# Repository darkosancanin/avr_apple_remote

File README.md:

### Overview 
ATtiny85 based micro controller project that replicates the functionality of an Apple remote control along with a simple hardware design for the remote control.

### Apple Remote/ NEC Protocol Overview
- The Apple Remote uses an NEC IR protocol which consists of a differential PPM encoding on a 1:3 duty cycle 38 kHz 950 nm infrared carrier.
- Remote commands are 32 bits long, in the format : remote id (8bits), command (8 bits), apple identifier (16 bits)
- The 32 bits of encoded data are sent between the leader and the stop bit (time in microseconds):
  - leader: 9000 on, 4500 off
  - 0 bit: 560 on, 1690 off
  - 1 bit: 560 on, 565 off
  - stop: 560 on
- More information at http://en.wikipedia.org/wiki/Apple_Remote and http://www.sbprojects.com/knowledge/ir/nec.php

### Implementation Overview
- This code uses a 50% duty cycle for the PWM (instead of the standard 1:3) for simplicity which still works.
- PWM is done using 'Clear Timer on Compare Match (CTC) Mode'. [Page 72] 11.7.2 describes CTC mode.
- Output is on 0C0A which is PB0. The internal clock is set to run at 8Mhz.
- No prescaler is used. @8Mhz 1 tick = .000000125 secs, 38khz is a cycle every .000026 secs. 
- This means there is 208 ticks required for a full cycle (.000026/.000000125). OCR0A is set to half of this at 104.
- This is half a full cycle, meaning it will be off for a half cycle, toggled due to COM0A0, and then on for a half cycle.
- We enable/disable PWM by enabling toggle on compare mode and then disconnecting OC0A and assuming normal port operation. [Page 78]
- The buttons are setup in a voltage ladder (http://en.wikipedia.org/wiki/Voltage_ladder). They are triggered via interrupts on PB4 and PB3 and each button is identified via a ADC conversion.
- The MCU is set to sleep in the main loop (using SLEEP_MODE_PWR_DOWN mode) and is only awoken using pin change interrupts.

### Button Voltage Ladder Values
Voltage ladder values (using 10 bit ADC resolution) on PB4
RIGHT:    0.00V @ 5V / 0.00V @ 3V / 0 (1.8K)
DOWN:     0.77V @ 5V / 0.46V @ 3V / 158 (330R)
MENU:     1.78V @ 5V / 1.08V @ 3V / 367 (680R)

Voltage ladder values (using 10 bit ADC resolution) on PB3
UP:      0.00V @ 5V / 0.00V @ 3V / 0 (1.8K)
LEFT:    0.77V @ 5V / 0.46V @ 3V / 158 (330R)
SELECT:  1.78V @ 5V / 1.08V @ 3V / 367 (680R)

### Schematic

### Breadboard

### PCB Layout

### Final Product

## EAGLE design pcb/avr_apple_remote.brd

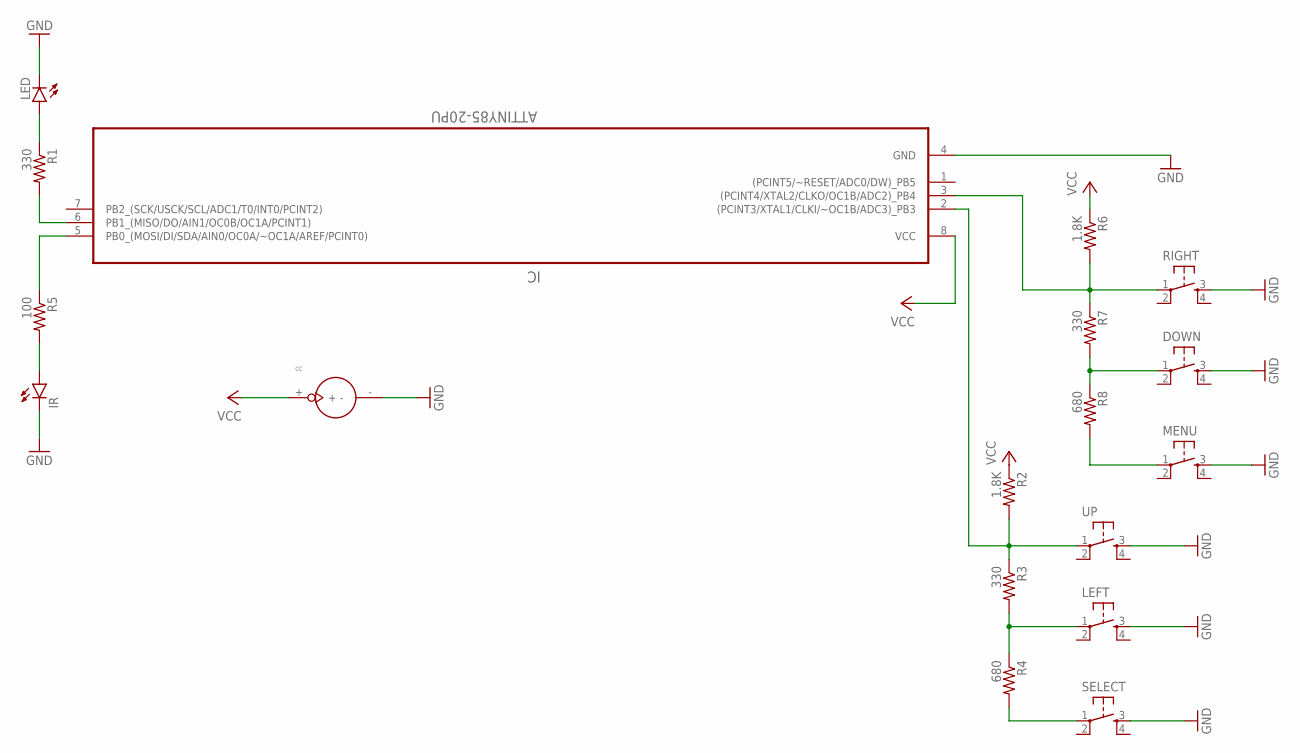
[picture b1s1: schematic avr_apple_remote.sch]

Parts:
CC: BATTERY_1236_C
DOWN: TACTILE-SWITCH-PTH; TAC-SWITCH-PTH
IC: ATTINY85-20PU; DIP254P762X533-8
IR: LED5MM
LED: LED5MM
LEFT: TACTILE-SWITCH-PTH; TAC-SWITCH-PTH
MENU: TACTILE-SWITCH-PTH; TAC-SWITCH-PTH
R1, R3, R7: 330; 0207/10
R2, R6: 1.8K; 0207/10
R4, R8: 680; 0207/10
R5: 100; 0207/10
RIGHT: TACTILE-SWITCH-PTH; TAC-SWITCH-PTH
SELECT: TACTILE-SWITCH-PTH; TAC-SWITCH-PTH
UP: TACTILE-SWITCH-PTH; TAC-SWITCH-PTH

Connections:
GND: CC.-, DOWN.3, IC.4 (GND), IR.K (C), LED.K (C), LEFT.3, MENU.3, RIGHT.3, SELECT.3, UP.3
unnamed: IC.3 ((PCINT4/XTAL2/CLKO/OC1B/ADC2)_PB4), R6.2, R7.1, RIGHT.1
unnamed: DOWN.1, R7.2, R8.1
unnamed: IC.2 ((PCINT3/XTAL1/CLKI/~OC1B/ADC3)_PB3), R2.2, R3.1, UP.1
unnamed: MENU.1, R8.2
unnamed: LEFT.1, R3.2, R4.1
unnamed: R4.2, SELECT.1
unnamed: IC.6 (PB1_(MISO/DO/AIN1/OC0B/OC1A/PCINT1)), R1.2
unnamed: LED.A, R1.1
unnamed: IC.5 (PB0_(MOSI/DI/SDA/AIN0/OC0A/~OC1A/AREF/P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), R5.1
unnamed: IR.A, R5.2
VCC: CC.+, IC.8 (VCC), R2.1, R6.1

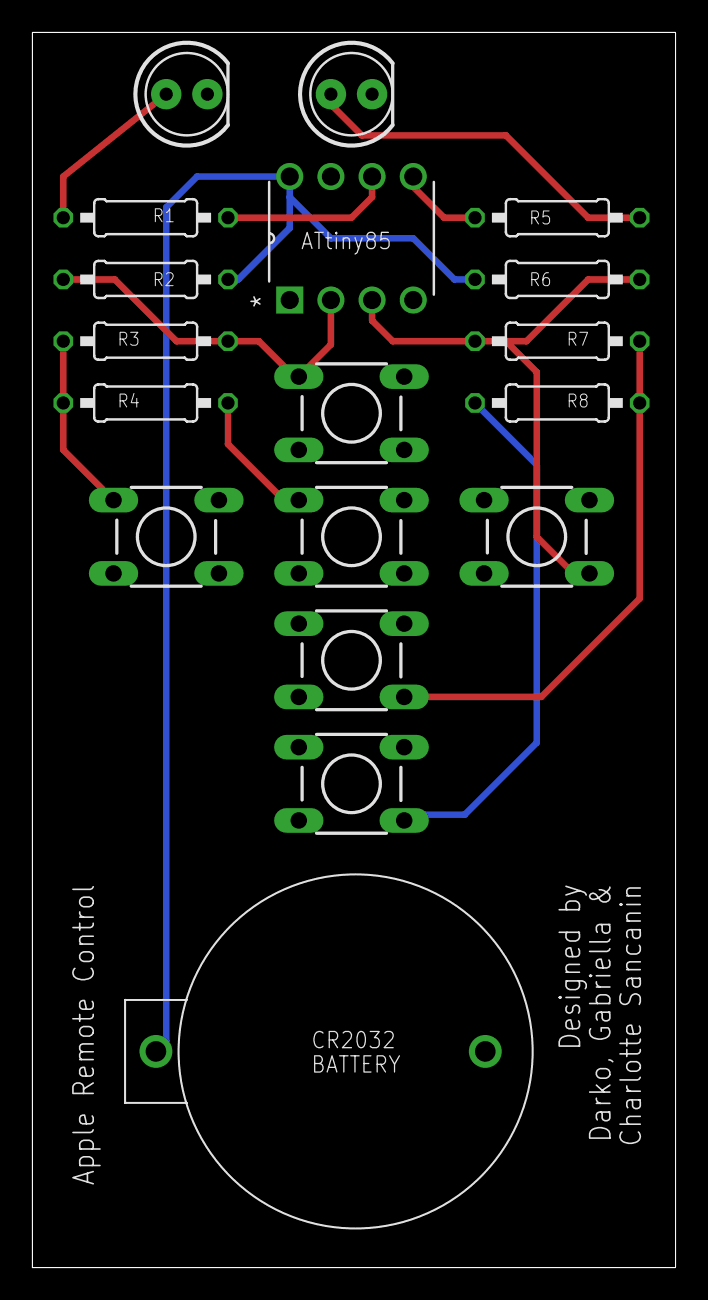
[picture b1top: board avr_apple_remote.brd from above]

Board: 2 copper layers, 39.7 x 76.2 mm, 18 parts (0 on the bottom side), 12 nets.

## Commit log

2011-01-10 Adding all initial files
2011-01-17 Converted remote code to be a library. Added a example application.
2011-01-17 Removed redundant file.
2015-03-09 Initial commit of v2 which uses a attiny85 @ 8Mhz.
2015-03-09 Added ATtiny85 datasheet.
2015-03-10 Updated to include ADC and match values for button presses.
2015-03-10 Reading the 10bit ADC value using the ADC register instead of ADCL and ADCH.
2015-03-10 Explicity set F_CPU to be unsigned long.
2015-03-12 Minor updates after initial testing.
2015-03-12 Updated voltage ladder values to be used with 1.8K resistor instead of 2K.
2015-03-14 Moved buttons 4 and 5 to a different pin as they werent triggering a interrupt as their voltage was not below half VCC.
2015-03-14 Added select button.
2015-03-14 Added status LED.
2015-03-14 Added minor comments.
2015-03-14 Removed pull up resistor test.
2015-03-14 Changed status LED to be on for the duration of the send command function.
2015-03-16 Put the chip into sleep mode when it is idle to minimize power consumption.
2015-03-16 Converted tab to spaces.
2015-03-17 Removed the enabling/disabling of interrupts on the ISR as I found out its automatically done.
2015-03-18 Updated some of the button voltage values after board layout reshuffle.
2015-03-18 Fixed status LED code.
2015-03-18 Added PCB design.
2015-03-18 Updated PCB design.
2015-03-18 Updated PCB design with final version - revision 1.0.
2015-04-15 Added read me file and images.
2015-04-15 Fixed read me formatting.
2015-04-15 Made headings in read me file smaller.
2015-04-15 Updated read me file formatting.
2015-06-11 Updated readme file."

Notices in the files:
parts and their libraries:
GeekAmmo: Licensing:Creative Commons ShareAlike 4.0 International - https://creativecommons.org/licenses/by-sa/4.0
